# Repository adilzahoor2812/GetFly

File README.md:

# ESP32 Quadcopter iOS Controller

SwiftUI iOS app to control an autonomous quadcopter over Wi‑Fi using an ESP32 microcontroller.

## Features

- Live drone status (position, battery, flight mode)
- Set target coordinates (X, Y, Z in meters)
- Tap the OpenStreetMap to pick coordinates (relative to your home point)
- Build and run multi-waypoint missions
- Flight controls: Arm, Disarm, Take Off, Land, Hover, Return Home, Emergency Stop
- Configurable ESP32 IP address and port

## Setup

1. Flash the ESP32 with the reference firmware in `firmware/esp32_quadcopter_server/`.
2. Connect your iPhone to the ESP32 Wi‑Fi network (`Quadcopter-ESP32` by default).
3. Open the app in Xcode and run on your device.
4. In **Settings** (gear icon), confirm the ESP32 address (default: `192.168.4.1:80`).

## HTTP API (ESP32)

### GET `/status`

```json
{
  "armed": false,
  "flying": false,
  "x": 0.0,
  "y": 0.0,
  "z": 0.0,
  "battery": 100,
  "mode": "idle",
  "message": "ok"
}
```

### POST `/command`

Go to a coordinate:

```json
{
  "action": "goto",
  "x": 2.0,
  "y": 1.5,
  "z": 1.5
}
```

Run a waypoint mission:

```json
{
  "action": "mission",
  "waypoints": [
    { "x": 1.0, "y": 0.0, "z": 1.5, "hold_seconds": 2.0 },
    { "x": 2.0, "y": 2.0, "z": 1.5, "hold_seconds": 2.0 }
  ]
}
```

Other actions: `arm`, `disarm`, `takeoff`, `land`, `hover`, `home`, `emergency_stop`.

Response:

```json
{ "success": true, "message": "Command accepted" }
```

## OpenStreetMap

The flight map uses **OpenStreetMap** tiles via MapKit. Set your **home point** in Settings:

1. Open **Settings** (gear icon)
2. Set home latitude/longitude, or tap **Use My Current Location**
3. Local X/Y (meters) are calculated east/north from home
4. Tap the map to set target coordinates

Map data © [OpenStreetMap](https://www.openstreetmap.org/copyright) contributors.

## Coordinate system

- **X**: forward (meters)
- **Y**: left/right (meters)
- **Z**: altitude (meters)

Origin (0, 0, 0) is the home/takeoff point.

## Project structure

```
Hike/
  Model/          - Coordinate, waypoint, command, status types
  Services/       - ESP32 HTTP client and connection settings
  ViewModel/      - DroneViewModel
  App Main/       - SwiftUI screens
firmware/         - ESP32 Arduino reference server
```

## Notes

- The included ESP32 sketch is a **reference server** — wire the TODO sections into your real motor/PID/autopilot code.
- iOS requires local network permission to reach the ESP32 on your LAN or AP.
- If your PDF specifies a different protocol, share it and the app can be adjusted to match.

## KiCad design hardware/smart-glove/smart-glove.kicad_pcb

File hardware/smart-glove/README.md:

# SignSpeak Smart Glove — MCU PCB (Rev H)

**Man Who Embed** · **72×52 mm** · ESP32 · **USB-C+CH340** · **DW01 protect** · 5× flex · MPU-6050 · 1.55 mm FR4

## Schematic
Open [`smart-glove.kicad_sch`](smart-glove.kicad_sch) — reference-style **labeled blocks** (USB-C, CH340, power, ESP32, flex, IMU, charge/protect).  
Preview: [`docs/schematic_preview.png`](docs/schematic_preview.png)  
Rebuild: `python3 build_complete_schematic.py`

## Rebuild

```bash
python3 build_complete_schematic.py
python3 build_production_v2.py
```

Fab: [`fab/SignSpeak_SmartGlove_RevH_Gerbers.zip`](fab/SignSpeak_SmartGlove_RevH_Gerbers.zip)

Firmware: [`../../firmware/signspeak_glove/`](../../firmware/signspeak_glove/)

### Docs
- [COMPLIANCE](docs/COMPLIANCE.md) · [ASSEMBLY](docs/ASSEMBLY.md) · [RF_MOUNTING](docs/RF_MOUNTING.md) · [BOM](BOM.md)

### Upload
Laptop → **USB-C** (CH340) → Arduino upload + Serial Monitor @ 115200  
Backup: **J4** UART header

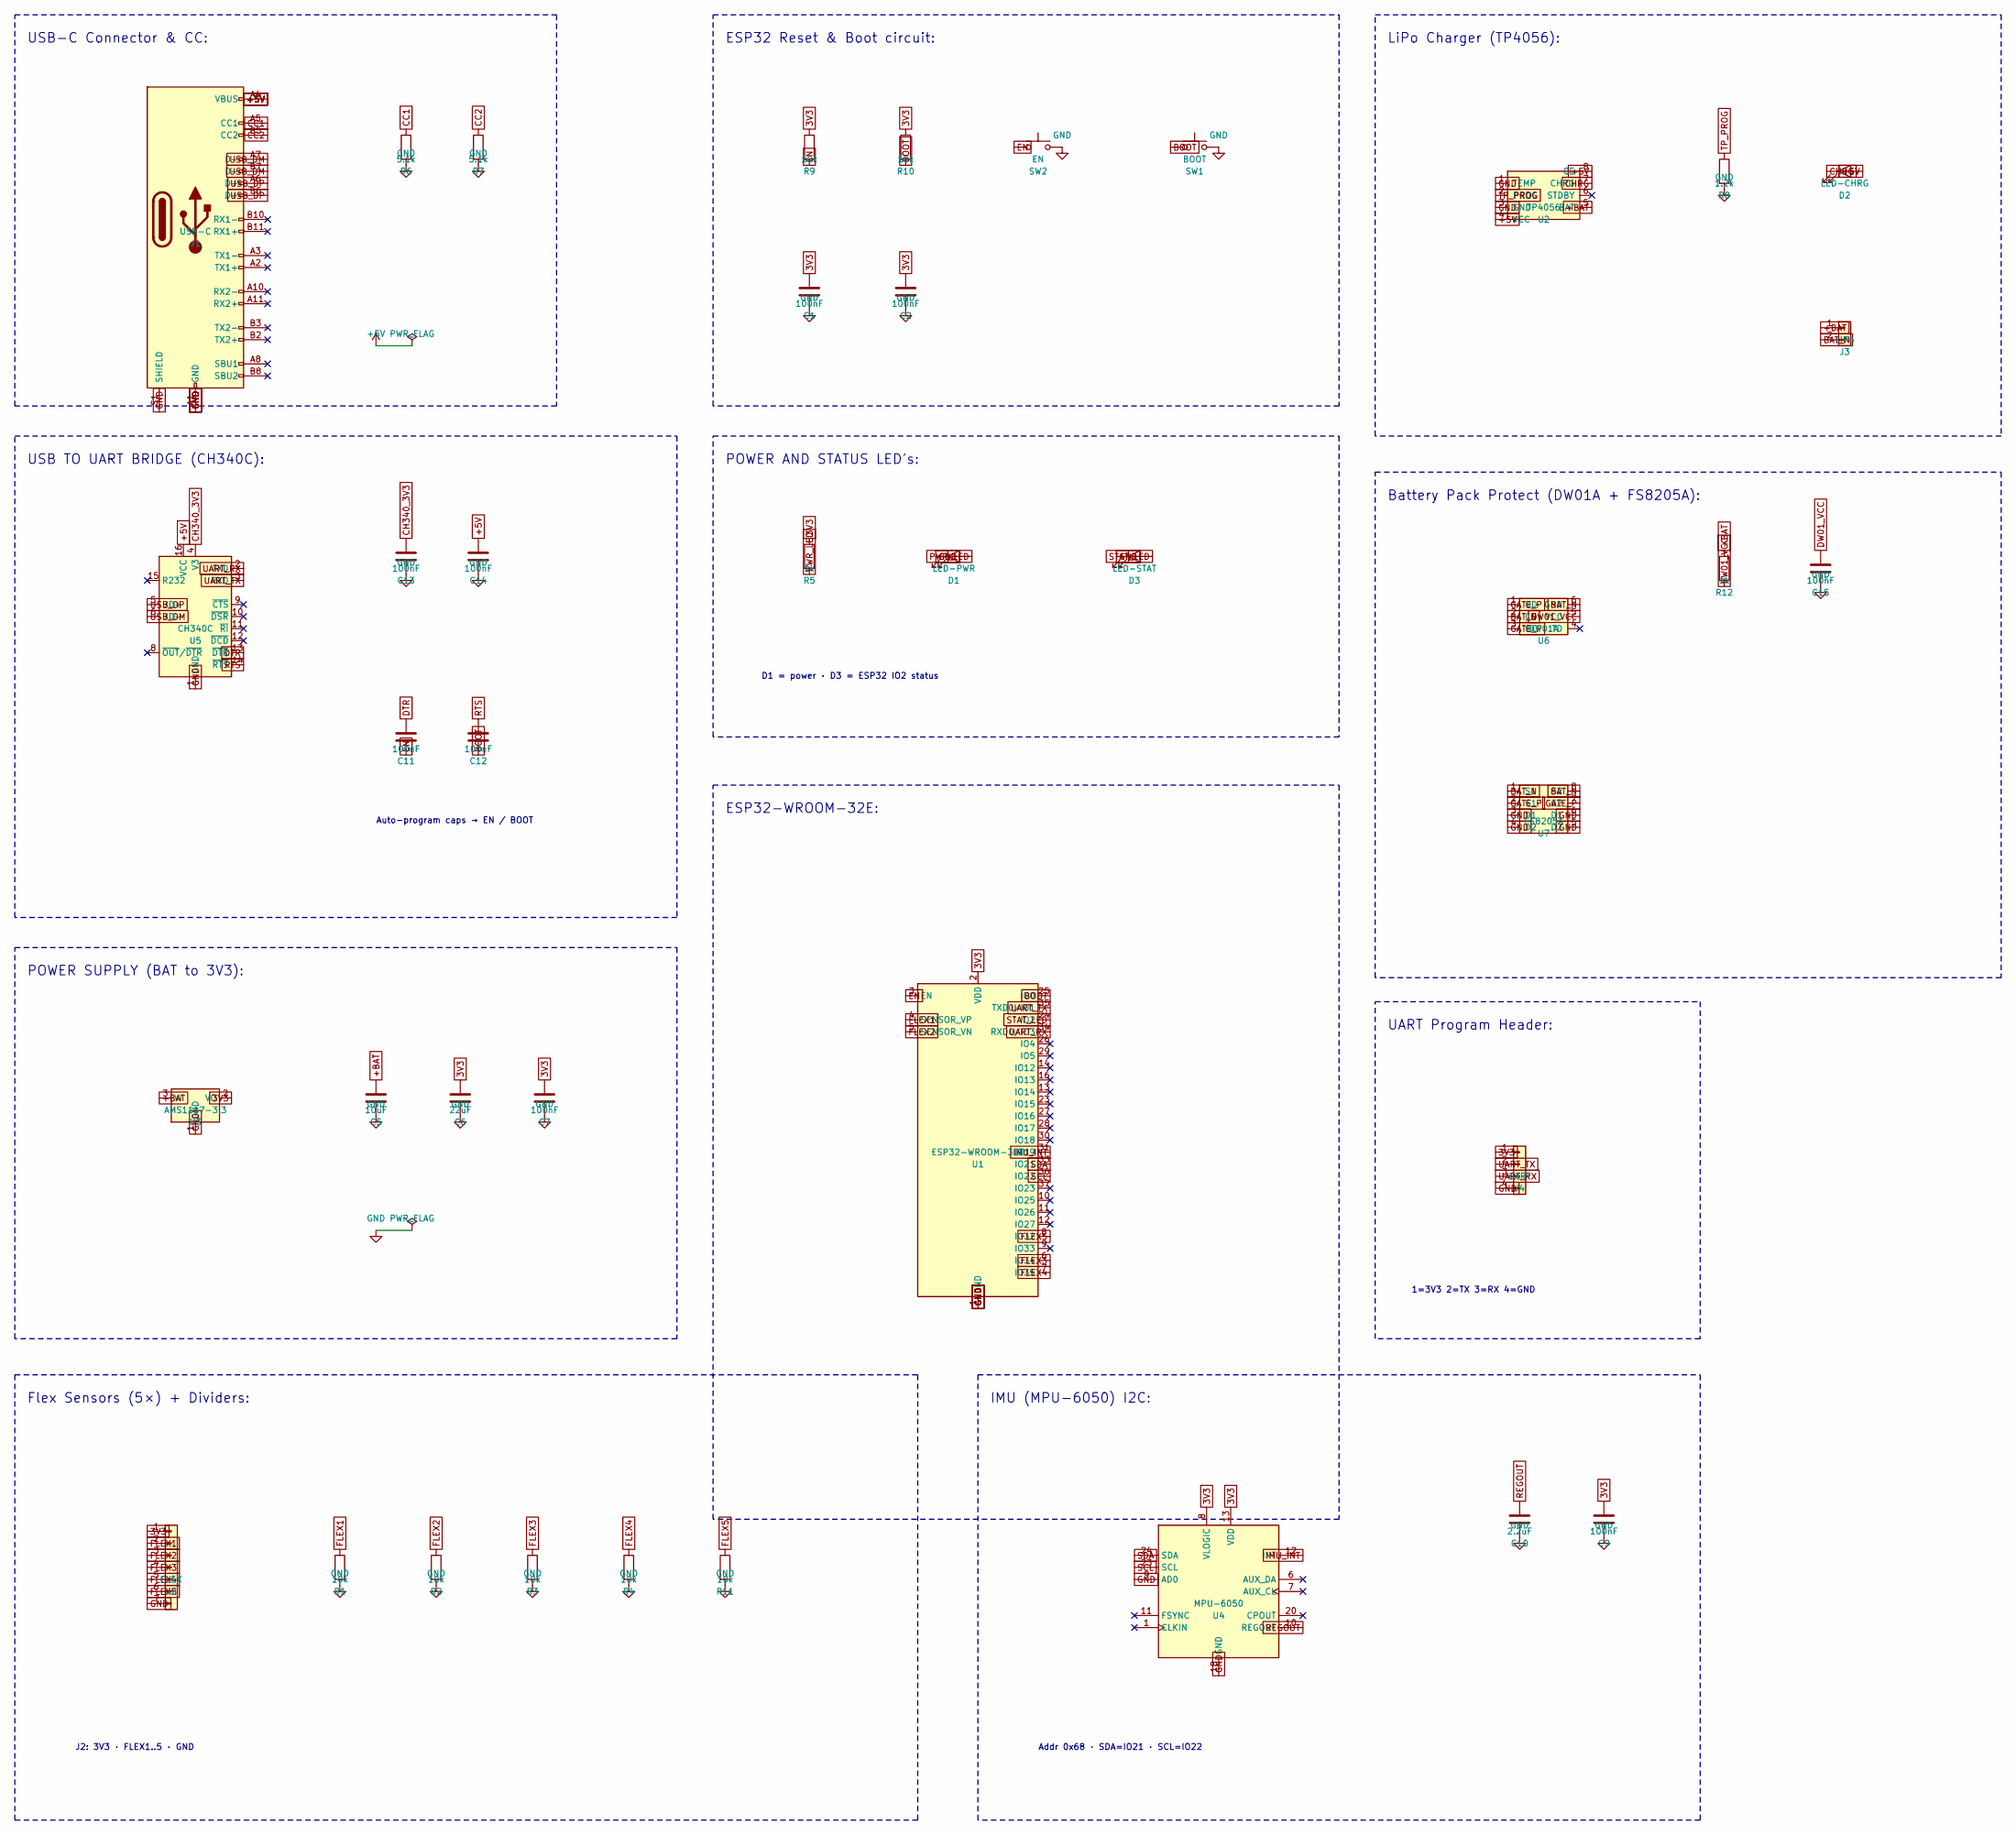
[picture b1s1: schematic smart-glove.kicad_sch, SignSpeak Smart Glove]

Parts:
C1, C2, C7, C9, C11, C12, C13, C14, C15: 100nF; C_0603_1608Metric
C5: 10uF; C_0805_2012Metric
C6: 22uF; C_0805_2012Metric
C10: 2.2uF; C_0805_2012Metric
D1: LED-PWR; LED_0603_1608Metric
D2: LED-CHRG; LED_0603_1608Metric
D3: LED-STAT; LED_0603_1608Metric
J1: USB-C; USB_C_Receptacle_HRO_TYPE-C-31-M-12
J2: FLEX; PinHeader_1x07_P2.54mm_Vertical
J3: LiPo; JST_PH_B2B-PH-K_1x02_P2.00mm_Vertical
J4: UART; PinHeader_1x04_P2.54mm_Vertical
R1, R2, R3, R4, R9, R10, R11: 10k; R_0603_1608Metric
R5, R12: 1k; R_0603_1608Metric
R6, R7: 5.1k; R_0603_1608Metric
R8: 1.2k; R_0603_1608Metric
SW1: BOOT; SW_SPST_B3U-1000P
SW2: EN; SW_SPST_B3U-1000P
U1: ESP32-WROOM-32E; ESP32-WROOM-32
U2: TP4056; SOIC-8_3.9x4.9mm_P1.27mm
U3: AMS1117-3.3; SOT-223
U4: MPU-6050; InvenSense_QFN-24_4x4mm_P0.5mm
U5: CH340C; SOIC-16_3.9x9.9mm_P1.27mm
U6: DW01A; SOT-23-6
U7: FS8205A; TSSOP-8_3x3mm_P0.65mm

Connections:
3V3: C1.1, C2.1, C6.1, C7.1, C9.1, J2.1, J4.1, R5.1, R9.1, R10.1, U1.2 (VDD), U3.2 (VO), U3.4, U4.8 (VLOGIC), U4.13 (VDD)
+5V: C14.1, D2.2 (A), J1.A4 (VBUS), J1.A9 (VBUS), J1.B4 (VBUS), J1.B9 (VBUS), U2.4 (VCC), U2.8 (CE), U5.16 (VCC)
+BAT: C5.1, J3.1, R12.1, U2.5 (BAT), U3.3 (VI)
BOOT: C12.2, R10.2, SW1.1, U1.25 (IO0)
CC1: J1.A5 (CC1), R6.1
CC2: J1.B5 (CC2), R7.1
CH340_3V3: C13.1, U5.4 (V3)
CHRG: D2.1 (K), U2.7 (CHRG)
DTR: C11.1, U5.13 (~DTR)
DW01_VCC: C15.1, R12.2, U6.5 (VCC)
EN: C11.2, R9.2, SW2.1, U1.3 (EN)
FLEX1: J2.2, R1.1, U1.4 (SENSOR_VP)
FLEX2: J2.3, R2.1, U1.5 (SENSOR_VN)
FLEX3: J2.4, R3.1, U1.6 (IO34)
FLEX4: J2.5, R4.1, U1.7 (IO35)
FLEX5: J2.6, R11.1, U1.8 (IO32)
GATE_P: U6.1 (OD), U6.3 (OC), U7.2 (G1), U7.7 (G2)
IMU_INT: U1.31 (IO19), U4.12 (INT)
PWR_LED: D1.2 (A), R5.2
REGOUT: C10.1, U4.10 (REGOUT)
RTS: C12.1, U5.14 (~RTS)
SCL: U1.36 (IO22), U4.23 (SCL)
SDA: U1.33 (IO21), U4.24 (SDA)
STAT_LED: D3.2 (A), U1.24 (IO2)
TP_PROG: R8.1, U2.2 (PROG)
UART_RX: J4.3, U1.34 (RXD0/IO3), U5.2 (TXD)
UART_TX: J4.2, U1.35 (TXD0/IO1), U5.3 (RXD)
USB_DM: J1.A7 (D-), J1.B7 (D-), U5.6 (UD-)
USB_DP: J1.A6 (D+), J1.B6 (D+), U5.5 (UD+)

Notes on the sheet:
USB-C Connector & CC:
USB TO UART BRIDGE (CH340C):
Auto-program caps → EN / BOOT
POWER SUPPLY (BAT to 3V3):
ESP32 Reset & Boot circuit:
POWER AND STATUS LED's:
D1 = power · D3 = ESP32 IO2 status
LiPo Charger (TP4056):
Battery Pack Protect (DW01A + FS8205A):
ESP32-WROOM-32E:
UART Program Header:
1=3V3 2=TX 3=RX 4=GND
Flex Sensors (5×) + Dividers:
J2: 3V3 · FLEX1..5 · GND
IMU (MPU-6050) I2C:
Addr 0x68 · SDA=IO21 · SCL=IO22

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
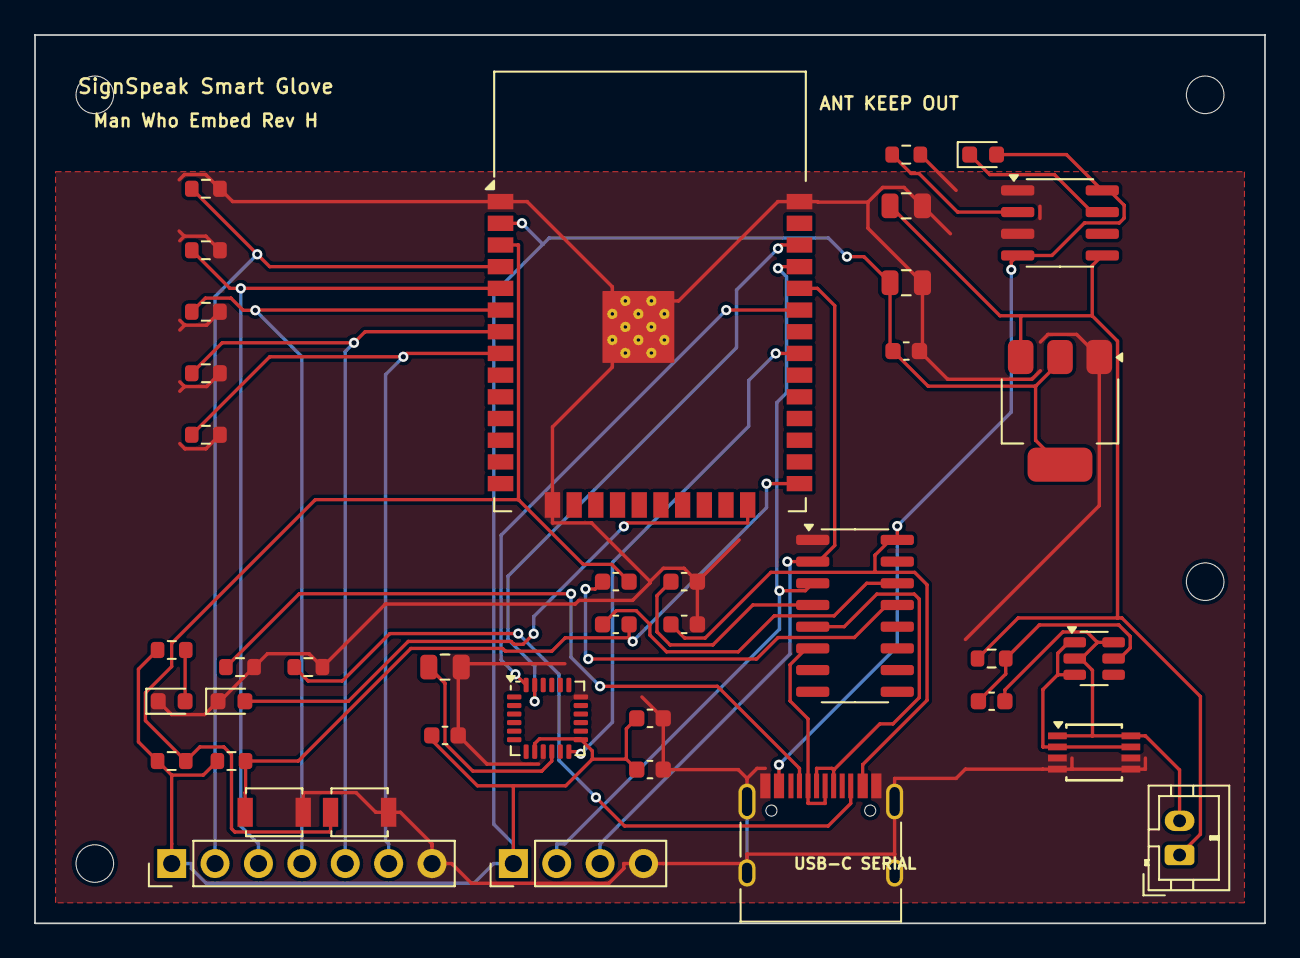
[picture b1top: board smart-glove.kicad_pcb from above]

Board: 2 copper layers, 72.0 x 52.0 mm, 44 parts (0 on the bottom side), 31 nets.

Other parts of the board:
H1, H2, H3, H4: M2; MountingHole_2.2mm_M2

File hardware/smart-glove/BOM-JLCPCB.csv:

Designator,Comment,Footprint,LCSC
C1,100nF,C_0603_1608Metric,C14663
C10,2.2uF,C_0805_2012Metric,C23629
C11,100nF,C_0603_1608Metric,C14663
C12,100nF,C_0603_1608Metric,C14663
C13,100nF,C_0603_1608Metric,C14663
C14,100nF,C_0603_1608Metric,C14663
C15,100nF,C_0603_1608Metric,C14663
C2,100nF,C_0603_1608Metric,C14663
C5,10uF,C_0805_2012Metric,C15850
C6,22uF,C_0805_2012Metric,C45783
C7,100nF,C_0603_1608Metric,C14663
C9,100nF,C_0603_1608Metric,C14663
D1,LED-PWR,LED_0603_1608Metric,C2290
D2,LED-CHRG,LED_0603_1608Metric,C2297
D3,LED-STAT,LED_0603_1608Metric,C2290
J1,USB-C,USB_C_Receptacle_HRO_TYPE-C-31-M-12,C165948
J2,FLEX,PinHeader_1x07_P2.54mm_Vertical,C492406
J3,LiPo,JST_PH_B2B-PH-K_1x02_P2.00mm_Vertical,C160402
J4,UART,PinHeader_1x04_P2.54mm_Vertical,C124378
R1,10k,R_0603_1608Metric,C25804
R10,10k,R_0603_1608Metric,C25804
R11,10k,R_0603_1608Metric,C25804
R12,1k,R_0603_1608Metric,C21190
R2,10k,R_0603_1608Metric,C25804
R3,10k,R_0603_1608Metric,C25804
R4,10k,R_0603_1608Metric,C25804
R5,1k,R_0603_1608Metric,C21190
R6,5.1k,R_0603_1608Metric,C23186
R7,5.1k,R_0603_1608Metric,C23186
R8,1.2k,R_0603_1608Metric,C22949
R9,10k,R_0603_1608Metric,C25804
SW1,BOOT,SW_SPST_B3U-1000P,C318884
SW2,EN,SW_SPST_B3U-1000P,C318884
U1,ESP32-WROOM-32E,ESP32-WROOM-32,C2934560
U2,TP4056,SOIC-8_3.9x4.9mm_P1.27mm,C16581
U3,AMS1117-3.3,SOT-223,C6186
U4,MPU-6050,InvenSense_QFN-24_4x4mm_P0.5mm,C24112
U5,CH340C,SOIC-16_3.9x9.9mm_P1.27mm,C84681
U6,DW01A,SOT-23-6,C351558
U7,FS8205A,TSSOP-8_3x3mm_P0.65mm,C351546

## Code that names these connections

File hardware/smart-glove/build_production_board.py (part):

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        elif n in {"A8", "B8"}:
            connect_pad(pad, nets["GND"])  # SBU unused → GND

    # TP4056 SOIC-8 pinout: 1 TEMP, 2 PROG, 3 GND, 4 VCC(USB), 5 BAT, 6 STDBY, 7 CHRG, 8 CE
    connect_pad(pad_by_number(u2, "1"), nets["GND"])  # TEMP to GND via 10k often; tie GND for simple
    connect_pad(pad_by_number(u2, "2"), nets["TP_PROG"])
    connect_pad(pad_by_number(u2, "3"), nets["GND"])
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    # tab pad sometimes "4"
    connect_pad(pad_by_number(u3, "4"), nets["3V3"])

    # MPU-6050 QFN-24 InvenSense: key pins - VDD, GND, SDA, SCL, AD0, INT, REGOUT, VLOGIC
    # Typical: pin8 VLOGIC, pin9 AD0, pin10 REGOUT, pin11 FSYNC, pin12 INT, pin13 VDD, pin18 GND, pin23 SCL, pin24 SDA
    # We'll assign known numbers from InvenSense footprint
    mpu_map = {
        "8": "3V3",   # VLOGIC
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        "1": "GND",
        "2": "3V3",
        "3": "EN",
        "4": "FLEX1",      # GPIO36 SENSOR_VP
        "5": "FLEX2",      # GPIO39 SENSOR_VN
        "6": "FLEX3",      # GPIO34
        "7": "FLEX4",      # GPIO35
        "15": "GND",
        "24": "STAT_LED",  # GPIO2
        "25": "BOOT",      # GPIO0
        "31": "IMU_INT",   # GPIO19
        "33": "SDA",       # GPIO21
        "34": "USB_DN",    # GPIO3 U0RXD (UART0 — use external USB-UART for programming)
        "35": "USB_DP",    # GPIO1 U0TXD
        "36": "GND",
        "37": "SCL",       # GPIO22
    }
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
```
J2-1 3V3 ──► Flex sensor HI (off-board)
Flex sense node ──► J2-2..5 (FLEX1..4) ──► ESP32 GPIO36/39/34/35
                 └─► R1..R4 10k ──► GND
```

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
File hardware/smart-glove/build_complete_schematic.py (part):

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      (pin power_in line (at -10.16 -5.08 0) (length 2.54) (name "VCC" (effects (font (size 1.27 1.27)))) (number "4" (effects (font (size 1.27 1.27)))))
      (pin power_out line (at 10.16 -2.54 180) (length 2.54) (name "BAT" (effects (font (size 1.27 1.27)))) (number "5" (effects (font (size 1.27 1.27)))))
      (pin passive line (at 10.16 0 180) (length 2.54) (name "STDBY" (effects (font (size 1.27 1.27)))) (number "6" (effects (font (size 1.27 1.27)))))
      (pin passive line (at 10.16 2.54 180) (length 2.54) (name "CHRG" (effects (font (size 1.27 1.27)))) (number "7" (effects (font (size 1.27 1.27)))))
      (pin passive line (at 10.16 5.08 180) (length 2.54) (name "CE" (effects (font (size 1.27 1.27)))) (number "8" (effects (font (size 1.27 1.27)))))
    )
  )'''
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    s.cap_to_gnd("C14", "100nF", 110.49, 127.0, "+5V")
    # Auto-program: DTR/RTS AC-coupled into EN/BOOT
    x, y = s.inst("Device:C", "C11", "100nF", 95.25, 165.1, "Capacitor_SMD:C_0603_1608Metric")
    s.label("DTR", x, y - 3.81, 90)
    s.label("EN", x, y + 3.81, 270)
    x, y = s.inst("Device:C", "C12", "100nF", 110.49, 165.1, "Capacitor_SMD:C_0603_1608Metric")
    s.label("RTS", x, y - 3.81, 90)
    s.label("BOOT", x, y + 3.81, 270)
    s.text("Auto-program caps → EN / BOOT", 88.9, 182.88, 1.27)

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    s.section("POWER AND STATUS LED's:", 160.02, 101.6, 292.1, 165.1)
    x, y = s.inst("Device:R", "R5", "1k", 180.34, 127.0, "Resistor_SMD:R_0603_1608Metric")
    s.label("3V3", x, y - 3.81, 90)
    s.label("PWR_LED", x, y + 3.81, 270)
    s.led_series("D1", "LED-PWR", 210.82, 127.0, "PWR_LED", "GND")
    s.led_series("D3", "LED-STAT", 248.92, 127.0, "STAT_LED", "GND")
    s.text("D1 = power · D3 = ESP32 IO2 status", 170.18, 152.4, 1.27)
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    u2x, u2y = g(335.28), g(50.8)
    s.inst("Device:TP4056", "U2", "TP4056", u2x, u2y, "Package_SO:SOIC-8_3.9x4.9mm_P1.27mm")
    s.label("GND", u2x - 10.16, u2y - 2.54, 0)
    s.label("TP_PROG", u2x - 10.16, u2y - 0.0, 0)
    s.label("GND", u2x - 10.16, u2y + 2.54, 0)
    s.label("+5V", u2x - 10.16, u2y + 5.08, 0)
    s.label("+BAT", u2x + 10.16, u2y + 2.54, 180)
    s.nc(u2x + 10.16, u2y - 0.0)
    s.label("CHRG", u2x + 10.16, u2y - 2.54, 180)
    s.label("+5V", u2x + 10.16, u2y - 5.08, 180)
    s.resistor_to_gnd("R8", "1.2k", 373.38, 45.72, "TP_PROG")
    s.led_series("D2", "LED-CHRG", 398.78, 45.72, "+5V", "CHRG")
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    s.inst("Connector_Generic:Conn_01x02", "J3", "LiPo", j3x, j3y,
           "Connector_JST:JST_PH_B2B-PH-K_1x02_P2.00mm_Vertical")
    s.label("+BAT", j3x - 5.08, j3y - 0.0, 0)
    s.label("BAT_N", j3x - 5.08, j3y + 2.54, 0)

    # ---- Battery Protection ----
    s.section("Battery Pack Protect (DW01A + FS8205A):", 300.0, 109.22, 431.8, 215.9)
    u6x, u6y = g(335.28), g(140.0)
    s.inst("Device:DW01A", "U6", "DW01A", u6x, u6y, "Package_TO_SOT_SMD:SOT-23-6")
    s.label("GATE_P", u6x - 7.62, u6y - 2.54, 0)
    s.label("BAT_N", u6x - 7.62, u6y - 0.0, 0)
    s.label("GATE_P", u6x - 7.62, u6y + 2.54, 0)
    s.nc(u6x + 7.62, u6y + 2.54)
    s.label("DW01_VCC", u6x + 7.62, u6y - 0.0, 180)
    s.label("BAT_N", u6x + 7.62, u6y - 2.54, 180)
    x, y = s.inst("Device:R", "R12", "1k", 373.38, 130.0, "Resistor_SMD:R_0603_1608Metric")
    s.label("+BAT", x, y - 3.81, 90)
    s.label("DW01_VCC", x, y + 3.81, 270)
    s.cap_to_gnd("C15", "100nF", 393.7, 130.0, "DW01_VCC")
    u7x, u7y = g(335.28), g(180.0)
    s.inst("Device:FS8205A", "U7", "FS8205A", u7x, u7y, "Package_SO:TSSOP-8_3x3mm_P0.65mm")
    s.label("BAT_N", u7x - 7.62, u7y - 3.81, 0)
    s.label("GATE_P", u7x - 7.62, u7y - 1.27, 0)
    s.label("GND", u7x - 7.62, u7y + 1.27, 0)
    s.label("GND", u7x - 7.62, u7y + 3.81, 0)
    s.label("GND", u7x + 7.62, u7y + 3.81, 180)
    s.label("GND", u7x + 7.62, u7y + 1.27, 180)
    s.label("GATE_P", u7x + 7.62, u7y - 1.27, 180)
    s.label("BAT_N", u7x + 7.62, u7y - 3.81, 180)

    # ---- ESP32 MCU (center) ----
    s.section("ESP32-WROOM-32E:", 160.02, 175.26, 292.1, 330.2)
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
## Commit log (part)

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2026-06-29 Add ESP32 quadcopter control iOS app with coordinate and waypoint support
    Build a SwiftUI controller that talks to an ESP32 over HTTP JSON:
    - Live status polling, coordinate input, tap-to-set map, and mission waypoints
    - Flight controls for arm/disarm, takeoff, land, goto, home, and emergency stop
    - Connection settings for ESP32 IP/port and local network permission
    - Reference Arduino firmware sketch matching the app API
2026-06-29 Fix DroneControlView buttonStyle compile error
    Replace mismatched ButtonStyle ternary with ViewBuilder branches for
    bordered and borderedProminent styles.
2026-06-29 Add OpenStreetMap to flight map with home point and geo coordinates
    Replace the grid map with OSM tiles via MapKit, convert local X/Y offsets
    to latitude/longitude from a configurable home point, and add location
    settings to set home from GPS.
2026-06-29 Apply remaining GetFly branding in demo and firmware comments
2026-06-30 Redesign GetFly UI with rich tab-based layout and design system
    Add GetFlyTheme and reusable components, reorganize into Dashboard,
    Navigate, Mission, and Controls tabs, and polish cards, telemetry,
    coordinate steppers, waypoint rows, settings, and toasts.
2026-06-30 Fix MKMarkerAnnotationView title compile error
    MKMarkerAnnotationView does not expose a title property. Annotation
    labels come from the MKAnnotation protocol, so move marker titles onto
    MapAnnotation as a computed title property.
2026-06-30 Add demo video HTML for GetFly map and mission changes
